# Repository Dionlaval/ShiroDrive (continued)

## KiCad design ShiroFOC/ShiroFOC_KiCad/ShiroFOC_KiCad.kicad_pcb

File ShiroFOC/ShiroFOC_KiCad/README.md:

# ShiroFOC A1-Drawing - schematic ready for prototype PCB layout

**P1 revision notes:** see [../PCB_REVISION_LIST_P1.md](../docs/PCB_REVISION_LIST_P1.md). H1-H4 are now in the schematic; the P0 PCB still awaits the mounting holes and placement revision. Earlier parity reports and release PDFs/ZIPs predate this change.

**PCB P0 placement is now available:** all 260 footprints on an 80 × 80 mm rounded-square, four-layer board. See [placement notes and previews](../docs/PCB_PLACEMENT_P0.md). Open the existing `.kicad_pcb`; it remains unrouted. The prior schematic release archives and manifests describe the earlier release, not this placement checkpoint.

Open `ShiroFOC_KiCad.kicad_pro` in **KiCad 9**. The project contains 12 native schematic sheets with connected functional blocks and project-local symbols/critical footprints. Standard footprints resolve through KiCad 9's installed libraries. A1-Drawing preserves all A0 electrical connections, components, values, MPNs, footprints and DNP choices.

Start with [design review](../docs/DESIGN_REVIEW_REV_A.md), [PCB layout handoff](../docs/PCB_LAYOUT_HANDOFF.md), and [firmware contract](../docs/FIRMWARE_BRINGUP_CONTRACT.md). No PCB has been routed. Current/voltage goals still require hardware qualification; the review identifies ripple, thermal, USB-power and braking limits.

## Release contents

- `libs/ShiroFOC_Redraw.kicad_sym`: functional symbols, including multi-unit STSPIN and analog switches, with complete physical pin mapping.
- `libs/ShiroFOC.pretty`: four datasheet-derived footprint types.
- `outputs/ShiroFOC_Rev_A_Schematic.pdf`: reviewed, searchable 12-page schematic (ten A3 and two A4 pages).
- `outputs/ShiroFOC_Rev_A_BOM.csv`: one row per reference, including DNP and procurement specifications.
- `outputs/ShiroFOC_Rev_A.net`: KiCad XML netlist.
- `outputs/erc_rev_a.json`, `validation_report.json`, `footprint_audit.json`, `footprint_pad_audit.csv`: release verification evidence.
- `outputs/electrical_calculations.json`: current-sense, brake-threshold, bus and rail calculations.
- `outputs/visual_review.json`, `release_manifest.json`: reviewed PDF/pages and SHA-256 release hashes.
- `outputs/net_name_aliases.json`: maps KiCad's local/hierarchical net names to the A0 names used by the handoff. Complete physical pin groups are verified independently of naming.
- `../review_baselines/A0_before_redraw/`: frozen connectivity and BOM used by the validator.

## Rebuild

Requires Python 3.12+ and KiCad 9 CLI, plus a Python interpreter containing `pcbnew`. From the ShiroFOC directory:

```sh
python3 tools/release_rev_a.py
```

On macOS the script discovers the standard `/Applications/KiCad/` installation. Other installations can set `KICAD_CLI`, `KICAD_PYTHON`, and `KICAD9_FOOTPRINT_DIR`. `KICAD_PYTHON` must import pcbnew. Set `FONTCONFIG_FILE` to a valid local fontconfig configuration if that installation needs one for headless PDF export.

`generate_rev_a.py` retains the electrical definitions. `native_rev_a.py` now delegates to `redraw_rev_a.py`; `redraw_core.py`, `redraw_power.py`, `redraw_analog.py` and `redraw_interfaces.py` define the connected drawings using `redraw_engine.py`. No legacy GUI conversion is needed. UUIDs are stable between redraw builds. **Rebuild overwrites generated native sheets and the redraw symbol library.** If editing in KiCad, also reconcile those changes into the layout modules before rebuilding. The checked-in custom footprints, project settings and handoff documents are preserved.

The overview contains navigable child sheets and graphic system connections. Circuit boundaries use named global ports; local circuits use wires and junctions. STSPIN units A/B/C/D/E/F remain one physical U301. See [redraw review](../docs/SCHEMATIC_REDRAW_REVIEW.md) for the sheet map and validation scope.

Rebuild regenerates machine checks but does not perform visual approval. Render and inspect the new PDF; refresh `visual_review.json` with its exact hash only after review, then run `python3 tools/release_rev_a.py --manifest-only`. That final command checks the visual hash and writes the release manifest. Keep review status separate from a successful CLI export.

## Start PCB layout

Continue from the existing P0 PCB. Use Update PCB from Schematic when synchronizing subsequent schematic changes. Keep all DNP footprints on-board; fitted state is controlled by the native DNP property and Assembly field. Follow the handoff for Kelvin routing, DC-link return points, live VIN thermal pads, optional termination and external connector restrictions. Preserve U901's documented thermal-drill adjustment when updating footprints. Resolve mechanical fit, copper/current sizing, DRC and fabrication details during PCB work.

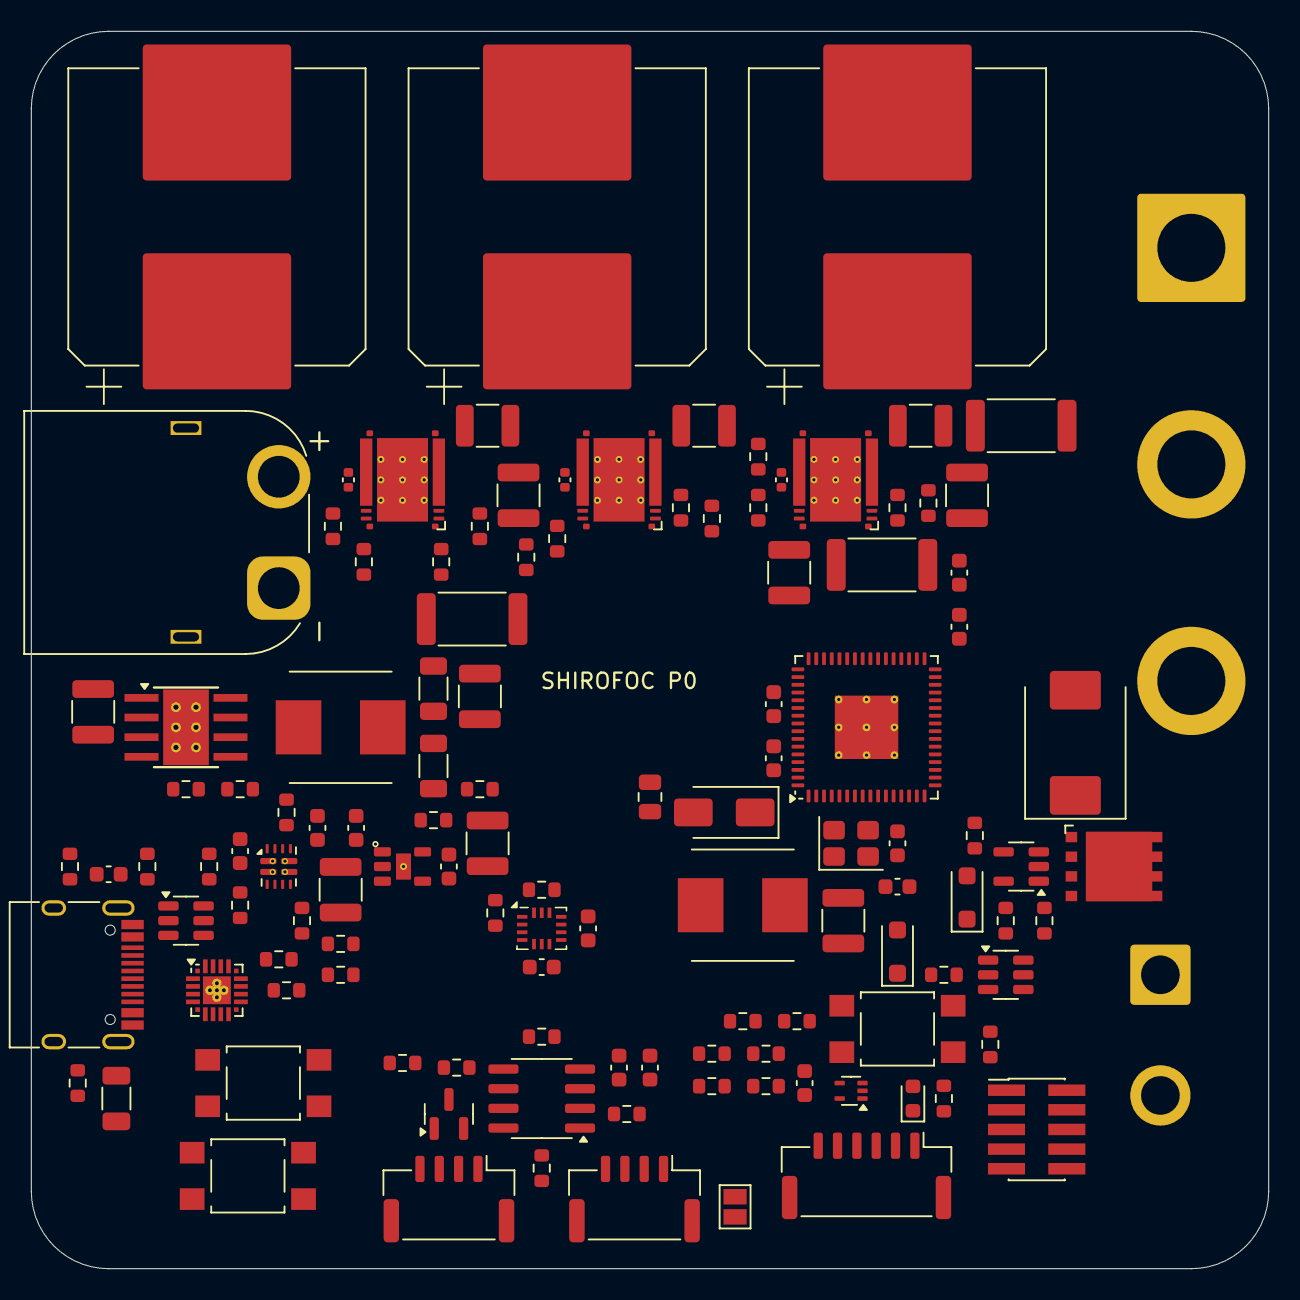
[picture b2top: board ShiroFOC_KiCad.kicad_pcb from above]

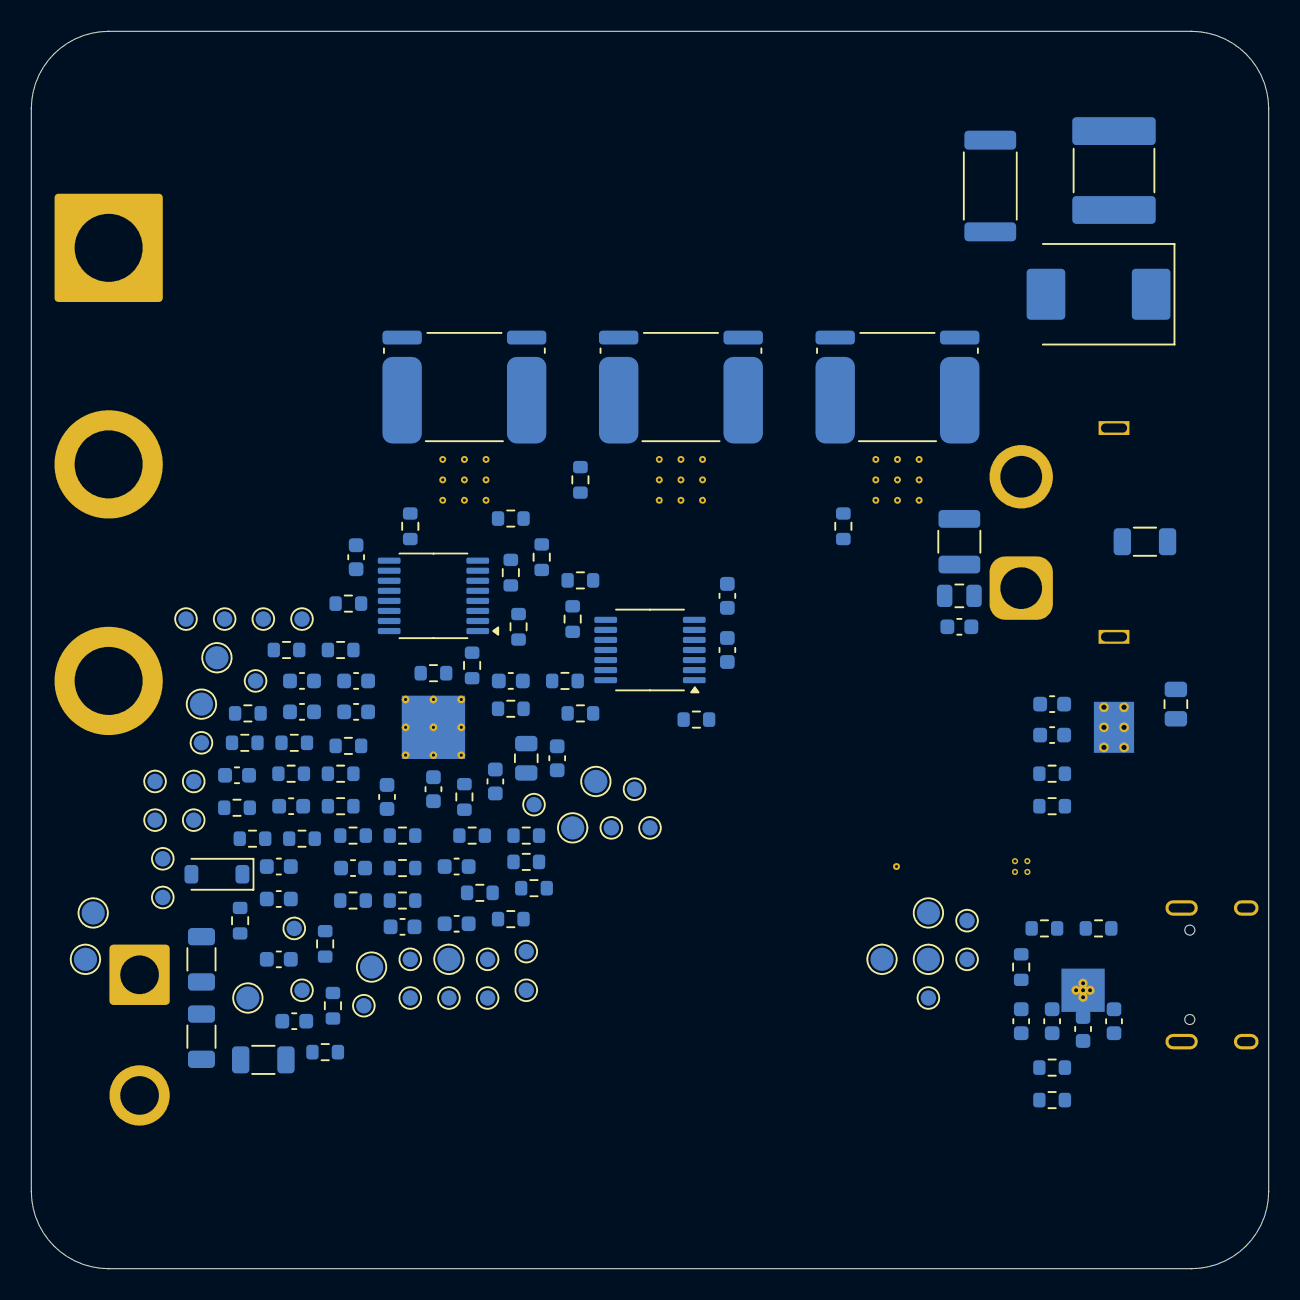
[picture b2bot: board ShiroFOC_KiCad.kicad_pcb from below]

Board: 4 copper layers, 80.0 x 80.0 mm, 260 parts (138 on the bottom side), 148 nets, no tracks yet.

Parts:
C101, C102, C103: 680uF 63V; CP_Elec_18x17.5
C104: 4.7uF 100V X7R; C_1210_3225Metric
C105: 100nF 100V X7R; C_0805_2012Metric
C106: 10nF 100V C0G; C_0603_1608Metric
C107: RC DAMP C - TUNE; C_2220_5750Metric
C108, C314, C711, C712, C713: 10nF; C_0603_1608Metric
C201: 2.2uF 100V X7R; C_1210_3225Metric
C202: 220nF 100V X7R; C_0805_2012Metric
C203, C209, C211, C301, C303, C305, C307, C310, C503, C601, C603, C701, C702, C801, C902, C904: 100nF; C_0603_1608Metric
C204, C304, C306, C602, C802: 1uF; C_0603_1608Metric
C205, C206, C210: 22uF 10V X7R; C_1210_3225Metric
C207: 4.7nF 2kV; C_1206_3216Metric
C208: 1uF 10V; C_0603_1608Metric
C212, C213: 2.2uF 10V X7R; C_0603_1608Metric
C302: 10uF 10V; C_0805_2012Metric
C308, C309: 10pF C0G; C_0603_1608Metric
C311: 220nF 100V; C_0805_2012Metric
C312: 10uF 25V X7R; C_1210_3225Metric
C313, C411, C421, C431, C502: 100nF 25V; C_0603_1608Metric
C412, C422, C432: 1uF 100V X7R; C_1210_3225Metric
C413, C423, C433: SNUBBER C TUNE; C_1210_3225Metric
C414, C424, C434: 47pF C0G; C_0603_1608Metric
C415, C425, C435: 10nF 100V X7S; C_0402_1005Metric
C501: 1uF 25V; C_0603_1608Metric
C504: 1nF C0G; C_0603_1608Metric
C604: 100nF 50V; C_0603_1608Metric
C901, C903: 4.7uF 10V; C_0603_1608Metric
D101: VM TVS - SELECT AFTER TEST; D_SMC
D301: RED; LED_0603_1608Metric
D302: STPS1H100A; D_SMA
D501: BZT52C12 12V; D_SOD-123
D502, D503: BAT54H; D_SOD-123F
D504: B5100C 100V 5A; D_SMC
D601: TPD3E001DRLR 3-line ESD; Texas_R-PDSO-N5_DRL-5
D801: PESD2CANFD24V-T; SOT-23
J101: AMASS XT60PW-M; AMASS_XT60PW-M_1x02_P7.20mm_Horizontal
J201: USB-C service; USB_C_Receptacle_HRO_TYPE-C-31-M-12
J401: MOTOR U/V/W; SolderWire-6sqmm_1x03_P14mm_D3.5mm_OD7mm
J501: BRAKE RESISTOR; SolderWire-2sqmm_1x02_P7.8mm_D2mm_OD3.9mm
J601: EXT ENCODER / HALL; JST_GH_BM06B-GHS-TBT_1x06-1MP_P1.25mm_Vertical
J801: CAN 1; JST_GH_BM04B-GHS-TBT_1x04-1MP_P1.25mm_Vertical
J802: CAN 2; JST_GH_BM04B-GHS-TBT_1x04-1MP_P1.25mm_Vertical
J1001: ARM Cortex SWD 10-pin; PinHeader_2x05_P1.27mm_Vertical_SMD
JP801: TERM ENABLE; SolderJumper-2_P1.3mm_Open_Pad1.0x1.5mm
L201, L301: 22uH / 2.75A; WE_LHMI_7050_74437349220
Q401, Q402, Q403: CSD88599Q5DC; CSD88599Q5DC_DMM0022A
Q501: CSD19531Q5A 100V; CSD19531Q5A_Q5A_DQJ0008A
R101: 470k 0.25W; R_1206_3216Metric
R102: RC DAMP R - TUNE; R_2512_6332Metric
R103, R104: 270k 0.1% 100V; R_1206_3216Metric
R105: 27k 0.1%; R_0603_1608Metric
R106, R304, R312, R711, R712, R713, R901, R1001: 1k; R_0603_1608Metric
R201: 100k 1%; R_0603_1608Metric
R202: 24.9k 1%; R_0603_1608Metric
R203, R204: 5.1k; R_0603_1608Metric
R205, R301, R302, R412, R422, R432: 0R; R_0603_1608Metric
R206: 15.0k 1%; R_0603_1608Metric
R207, R209, R211, R213: 5.10k 1%; R_0603_1608Metric
R208: 10.0k 1%; R_0603_1608Metric
R210, R212: 21.0k 1%; R_0603_1608Metric
R214: 80.6k 1%; R_0603_1608Metric
R215, R305, R306, R307, R308, R309, R311, R501, R504, R505, R801, R805: 10k; R_0603_1608Metric
R303, R310, R413, R414, R423, R424, R433, R434: 100k; R_0603_1608Metric
R313, R314: 22R; R_0603_1608Metric
R410, R420, R430, R441, R442, R443: 56k 0.1%; R_0603_1608Metric
R411, R421, R431, R503: 4.7R; R_0603_1608Metric
R415, R425, R435: SNUBBER R TUNE; R_2512_6332Metric
R416, R426, R436: BVR-Z-R0005 0.5mR; R_Shunt_Isabellenhuette_BVR4026
R417, R418, R427, R428, R437, R438: 1k 0.1%; R_0603_1608Metric
R419, R429, R439: 28k 0.1%; R_0603_1608Metric
R502, R601, R602, R603, R611, R714: 33R; R_0603_1608Metric
R506, R507, R508: 150k 0.1% 100V; R_1206_3216Metric
R509: 12.7k 0.1%; R_0603_1608Metric
R510: 1M 0.1%; R_0603_1608Metric
R604: 0R; external load <=25mA; R_0603_1608Metric
R605, R606, R607, R902, R903: 100R; R_0603_1608Metric
R608, R609, R610: 10k DNP Hall pull-up; R_0603_1608Metric
R701, R702, R703: 4.7k 1%; R_0603_1608Metric
R802: 120R 1%; R_0603_1608Metric
R803: 0R CANH link; R_0603_1608Metric
R804: 0R CANL link; R_0603_1608Metric
R904: 22.1k 1%; R_0603_1608Metric
R905: 47.5k 1%; R_0603_1608Metric
SW301, SW1002: RESET; SW_SPST_TL3305A
SW1001: BOOT0; SW_SPST_TL3305A
TH701, TH702, TH703: 10k NTC B3380; R_0603_1608Metric
TP101: VM; TestPoint_Pad_D1.5mm
TP102: GND; TestPoint_Pad_D1.5mm
TP103: VBUS_SENSE; TestPoint_Pad_D1.5mm
TP201: 5V_BAT; TestPoint_Pad_D1.5mm
TP202: 5V_USB; TestPoint_Pad_D1.5mm
TP203: 5V_SYS; TestPoint_Pad_D1.5mm
TP204: 3V3; TestPoint_Pad_D1.5mm
TP301: VCC; TestPoint_Pad_D1.5mm
TP302: SCREF; TestPoint_Pad_D1.5mm
TP303: NRST; TestPoint_Pad_D1.5mm
TP501: BRAKE_GATE; TestPoint_Pad_D1.5mm
TP502: BRK_SW; TestPoint_Pad_D1.5mm
TP701: NTC_A; TestPoint_Pad_D1.0mm
TP702: NTC_B; TestPoint_Pad_D1.0mm
TP703: NTC_C; TestPoint_Pad_D1.0mm
TP901: USB_UART_TX; TestPoint_Pad_D1.0mm
TP902: USB_UART_RX; TestPoint_Pad_D1.0mm
TP903: GND; TestPoint_Pad_D1.0mm
TP1001: VM; TestPoint_Pad_D1.0mm
TP1002: VCC; TestPoint_Pad_D1.0mm
TP1003: 5V_BAT; TestPoint_Pad_D1.0mm
TP1004: 5V_USB; TestPoint_Pad_D1.0mm
TP1005: 5V_SYS; TestPoint_Pad_D1.0mm
TP1006: 3V3; TestPoint_Pad_D1.0mm
TP1007: NRST; TestPoint_Pad_D1.0mm
TP1008: SWDIO; TestPoint_Pad_D1.0mm
TP1009: SWCLK; TestPoint_Pad_D1.0mm
TP1010: SPI3_SCK; TestPoint_Pad_D1.0mm
TP1011: SPI3_MISO; TestPoint_Pad_D1.0mm
TP1012: SPI3_MOSI; TestPoint_Pad_D1.0mm
TP1013: FDCAN1_TX; TestPoint_Pad_D1.0mm
TP1014: FDCAN1_RX; TestPoint_Pad_D1.0mm
TP1015: FEEDBACK_A_H1; TestPoint_Pad_D1.0mm
TP1016: FEEDBACK_B_H2; TestPoint_Pad_D1.0mm
TP1018: OPO_U1; TestPoint_Pad_D1.0mm
TP1019: OPO_V1; TestPoint_Pad_D1.0mm
TP1020: OPO_W1; TestPoint_Pad_D1.0mm
TP1021: SPARE_GPIO_1; TestPoint_Pad_D1.0mm
TP1022: CAN_STB; TestPoint_Pad_D1.0mm
TP1023: SPARE_GPIO_3; TestPoint_Pad_D1.0mm
TP1024: SPARE_TIM_GPIO; TestPoint_Pad_D1.0mm
U201: LMR36510FADDAR; Texas_HTSOP-8-1EP_3.9x4.9mm_P1.27mm_EP2.95x4.9mm_Mask2.4x3.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
U202: USBLC6-2SC6; SOT-23-6
U203: TPS2121RUXR; Texas_VQFN-HR-12_2x2.5mm_P0.5mm_ThermalVias
U204: TLV75533PDYDR; Texas_DYD0005A_SOT23-5
U301: STSPIN32G4; QFN-64-1EP_9x9mm_P0.5mm_EP4.1x4.1mm_ThermalVias
U501: UCC27517ADBVR; SOT-23-5
U502: TLV3012BIDBVR; SOT-23-6
U601: AS5047P-ATSM; TSSOP-14_4.4x5mm_P0.65mm
U602: TMUX1574PW; TSSOP-16_4.4x5mm_P0.65mm
U701: BMI323; Bosch_LGA-14_3x2.5mm_P0.5mm
U801: TCAN3413DR; SOIC-8_3.9x4.9mm_P1.27mm
U901: CP2102N-A02-GQFN20; SiliconLabs_QFN-20-1EP_3x3mm_P0.5mm_EP1.8x1.8mm_ThermalVias
Y301: 24MHz 7pF; Crystal_SMD_3225-4Pin_3.2x2.5mm

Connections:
3V3: C213.1, C301.1, C302.1, C307.1, C503.1, C601.1, C602.1, C603.1, C701.1, C702.1, C801.1, C802.1, C901.1, C902.1, C903.1, C904.1, J1001.1, R215.1, R301.1, R303.1, R304.1, R305.1, R308.1, R309.1, R310.1, R604.1, R608.1, R609.1, R610.1, R701.1, R702.1, R703.1, R801.1, R805.1, R901.1, SW1001.2, TP204.1, TP1006.1, U204.5, U301.1, U301.2, U301.64, U502.6, U601.11, U601.12, U602.16, U701.5, U701.8, U801.3, U801.5, U901.6, U901.7
5V_BAT: C205.1, C206.1, L201.2, R201.1, R206.1, R210.1, TP201.1, TP1003.1, U203.7
5V_SYS: C210.1, C211.1, C212.1, TP203.1, TP1005.1, U203.1, U203.8, U204.1, U204.3
5V_USB: C208.1, R205.2, R208.1, R212.1, TP202.1, TP1004.1, U203.2
5V_USB_RAW: J201.A4, J201.A9, J201.B4, J201.B9, R205.1, R904.1, U202.5
/5 V / 3.3 V power/5V_FB: R201.2, R202.1, U201.5
/Brake chopper/BRAKE_OV_CMD: D503.2, R510.1, U502.1
/Brake chopper/BRAKE_PWM_DRV: D502.1, D503.1, R505.1, U501.3
/CAN interface/CANH_BUS: D801.1, J801.3, J802.3, R802.1, R803.2
/CAN interface/CANH_INT: R803.1, U801.7
/CAN interface/CANL_BUS: D801.2, J801.2, J802.2, JP801.2, R804.2
/CAN interface/CANL_INT: R804.1, U801.6
/CAN interface/CAN_SHIELD: J801.4, J802.4
/CAN interface/CAN_TERM_MID: JP801.1, R802.2
/Current / temperature/NTC_A_RAW: R701.2, R711.1, TH701.1
/Current / temperature/NTC_B_RAW: R702.2, R712.1, TH702.1
/Current / temperature/NTC_C_RAW: R703.2, R713.1, TH703.1
/Current / temperature/OPN_U1: C414.2, R418.2, R419.2, U301.16
/Current / temperature/OPN_V1: C424.2, R428.2, R429.2, U301.22
/Current / temperature/OPN_W1: C434.2, R438.2, R439.2, U301.25
/Current / temperature/OPP_U1: R410.2, R417.2, R441.1, U301.14
/Current / temperature/OPP_V1: R420.2, R427.2, R442.1, U301.20
/Current / temperature/OPP_W1: R430.2, R437.2, R443.1, U301.23
/Feedback selection/3V3_EXT_FB: J601.1, R604.2
/Feedback selection/FB_ESD_RAIL: C604.1, D601.5
/Feedback selection/MUX_EXT_A: R605.2, R608.2, U602.3
/Feedback selection/MUX_EXT_B: R606.2, R609.2, U602.6
/Feedback selection/MUX_EXT_I: R607.2, R610.2, U602.10
/MCU / clock / SWD/NRST: C310.1, J1001.10, R303.2, SW301.1, SW1002.1, TP303.1, TP1007.1, U301.8
/MCU / clock / SWD/SPARE_GPIO_1: TP1021.1, U301.5
/MCU / clock / SWD/SPARE_GPIO_3: TP1023.1, U301.3
/MCU / clock / SWD/SPARE_TIM_GPIO: TP1024.1, U301.44
/SPI sensors/AS5047_MISO_RAW: R611.1, U601.3
/SPI sensors/BMI323_MISO_RAW: R714.1, U701.1
/SPI sensors/ENC_ON_A: R601.1, U601.7
/SPI sensors/ENC_ON_B: R602.1, U601.6
/SPI sensors/ENC_ON_I: R603.1, U601.14
/SPI sensors/SPI3_MOSI: R314.2, TP1012.1, U601.4, U701.14
/SPI sensors/SPI3_SCK: R313.2, TP1010.1, U601.2, U701.13
/Three-phase bridge/SHUNT_U_FORCE_P: C415.2, Q401.12, Q401.13, Q401.14, Q401.15, Q401.16, Q401.17, Q401.18, Q401.19, Q401.20, R414.2, R416.1
/Three-phase bridge/SHUNT_V_FORCE_P: C425.2, Q402.12, Q402.13, Q402.14, Q402.15, Q402.16, Q402.17, Q402.18, Q402.19, Q402.20, R424.2, R426.1
/Three-phase bridge/SHUNT_W_FORCE_P: C435.2, Q403.12, Q403.13, Q403.14, Q403.15, Q403.16, Q403.17, Q403.18, Q403.19, Q403.20, R434.2, R436.1
/USB service/CP2102_RST_N: R901.2, U901.9
/USB service/CP2102_VBUS_SENSE: R904.2, R905.1, U901.8
/USB service/UART_BRIDGE_RX: R903.2, U901.17
/USB service/UART_BRIDGE_TX: R902.1, U901.18
/USB service/USB_CC1: J201.A5, R203.1
/USB service/USB_CC2: J201.B5, R204.1
/USB service/USB_DM: U202.6, U901.5
/USB service/USB_DM_CONN: J201.A7, J201.B7, U202.1
/USB service/USB_DP: U202.4, U901.4
/USB service/USB_DP_CONN: J201.A6, J201.B6, U202.3
/USB service/USB_SHIELD: C207.1, J201.S1
AS5047P_CS_N: R309.2, U301.51, U601.1
BOOT1: C411.1, U301.41
BOOT2: C421.1, U301.38
BOOT3: C431.1, U301.35
BRAKE_PWM: R501.1, R502.1, U301.60
CAN_STB: R801.2, TP1022.1, U301.28, U801.8
FDCAN1_RX: TP1014.1, U301.47, U801.4
FDCAN1_TX: R805.2, TP1013.1, U301.48, U801.1
FEEDBACK_A_H1: TP1015.1, U301.57, U602.4
FEEDBACK_B_H2: TP1016.1, U301.58, U602.7
FEEDBACK_ENABLE_N: R305.2, U301.4, U602.15
FEEDBACK_I_H3: R307.1, R1001.1, U301.59, U602.9
FEEDBACK_SELECT: R306.1, U301.53, U602.1
GHS1: R411.1, U301.43
GHS2: R421.1, U301.40
GHS3: R431.1, U301.37
GLS1: R412.1, U301.29
GLS2: R422.1, U301.30
GLS3: R432.1, U301.31
GND: C101.2, C102.2, C103.2, C104.2, C105.2, C106.2, C107.2, C108.2, C201.2, C202.2, C204.2, C205.2, C206.2, C207.2, C208.2, C209.2, C210.2, C211.2, C212.2, C213.2, C301.2, C302.2, C303.2, C304.2, C305.2, C306.2, C307.2, C308.2, C309.2, C310.2, C311.2, C312.2, C313.2, C314.2, C412.2, C413.2, C422.2, C423.2, C432.2, C433.2, C501.2, C502.2, C503.2, C504.2, C601.2, C602.2, C603.2, C604.2, C701.2, C702.2, C711.2, C712.2, C713.2, C801.2, C802.2, C901.2, C902.2, C903.2, C904.2, D101.2, D302.2, D501.2, D601.3, D801.3, J101.1, J201.A1, J201.A12, J201.B1, J201.B12, J601.2, J801.1, J802.1, J1001.3, J1001.5, J1001.9, Q501.1, Q501.2, Q501.3, R101.2, R105.2, R202.2, R203.2, R204.2, R207.2, R209.2, R211.2, R213.2, R214.2, R306.2, R307.2, R311.2, R416.4, R426.4, R436.4, R441.2, R442.2, R443.2, R501.2, R504.2, R505.2, R509.2, R905.2, SW301.2, SW1002.2, TH701.2, TH702.2, TH703.2, TP102.1, TP903.1, U201.1, U201.9, U202.2, U203.12, U204.2, U301.32, U301.65, U501.2, U501.4, U502.2, U601.5, U601.13, U602.8, U701.6, U701.7, U801.2, U901.3, U901.12, U901.21, Y301.2, Y301.4
IMU_CS_N: R308.2, U301.21, U701.12
IMU_INT1: U301.17, U701.4
IMU_INT2: U301.18, U701.9
MUX_ON_A: R601.2, U602.2
MUX_ON_B: R602.2, U602.5
MUX_ON_I: R603.2, U602.11
NTC_PHASE_A: C711.1, R711.2, TP701.1, U301.12
NTC_PHASE_B: C712.1, R712.2, TP702.1, U301.9
NTC_PHASE_C: C713.1, R713.2, TP703.1, U301.10
unnamed: C107.1, R102.2
unnamed: C413.1, R415.2
unnamed: C423.1, R425.2
unnamed: C433.1, R435.2
unnamed: D301.2, R304.2
unnamed: D301.1, U301.11
unnamed: D302.1, L301.1, U301.62
unnamed: D501.1, Q501.4, R503.2, R504.1, TP501.1
unnamed: D502.2, R502.2
unnamed: D504.2, J501.2, Q501.5, Q501.6, Q501.7, Q501.8, TP502.1
unnamed: D601.1, J601.3, R605.1
unnamed: D601.2, J601.4, R606.1
unnamed: D601.4, J601.5, R607.1
unnamed: Q401.1, R411.2, R413.1
unnamed: Q401.22, R412.2, R414.1
unnamed: Q402.1, R421.2, R423.1
unnamed: Q402.22, R422.2, R424.1
unnamed: Q403.1, R431.2, R433.1
unnamed: Q403.22, R432.2, R434.1
unnamed: R103.2, R104.1
unnamed: R104.2, R105.1, R106.1
unnamed: R310.2, R311.1, R312.1
unnamed: R506.2, R507.1
unnamed: R507.2, R508.1
unnamed: R1001.2, SW1001.1
unnamed: C203.1, U201.7
unnamed: C203.2, L201.1, U201.8
unnamed: C204.1, U201.6
unnamed: R208.2, R209.1, U203.3
unnamed: R214.1, U203.10
unnamed: R210.2, R211.1, U203.5
unnamed: R212.2, R213.1, U203.4
unnamed: R206.2, R207.1, U203.6
unnamed: C209.1, U203.11
unnamed: J1001.2, TP1008.1, U301.49
unnamed: J1001.4, TP1009.1, U301.50
unnamed: C308.1, U301.6, Y301.1
unnamed: C309.1, U301.7, Y301.3
unnamed: C314.1, R312.2, TP302.1, U301.52
unnamed: R503.1, U501.5
unnamed: C504.1, R508.2, R509.1, R510.2, U502.3
unnamed: U502.4, U502.5
OPO_U1: C414.1, R419.1, TP1018.1, U301.15
OPO_V1: C424.1, R429.1, TP1019.1, U301.19
OPO_W1: C434.1, R439.1, TP1020.1, U301.24
OUT1: C411.2, J401.1, Q401.2, Q401.3, Q401.4, Q401.5, Q401.6, Q401.7, Q401.8, Q401.9, Q401.10, Q401.11, R413.2, R415.1, U301.42
OUT2: C421.2, J401.2, Q402.2, Q402.3, Q402.4, Q402.5, Q402.6, Q402.7, Q402.8, Q402.9, Q402.10, Q402.11, R423.2, R425.1, U301.39
OUT3: C431.2, J401.3, Q403.2, Q403.3, Q403.4, Q403.5, Q403.6, Q403.7, Q403.8, Q403.9, Q403.10, Q403.11, R433.2, R435.1, U301.36
PWR_SOURCE_STATUS: R215.2, U203.9
SHUNT_U_SENSE_N: R416.3, R418.1
SHUNT_U_SENSE_P: R416.2, R417.1
SHUNT_V_SENSE_N: R426.3, R428.1
SHUNT_V_SENSE_P: R426.2, R427.1
SHUNT_W_SENSE_N: R436.3, R438.1
SHUNT_W_SENSE_P: R436.2, R437.1
SPI3_MISO: R611.2, R714.2, TP1011.1, U301.55
SPI3_MOSI_MCU: R314.1, U301.56
SPI3_SCK_MCU: R313.1, U301.54
USB_UART_RX: R902.2, TP902.1, U301.46
USB_UART_TX: R903.1, TP901.1, U301.45
VBUS_MUX_IN: R106.2, U602.13, U602.14
VBUS_SENSE: C108.1, TP103.1, U301.13, U602.12
VCC: C312.1, C313.1, C501.1, C502.1, L301.2, TP301.1, TP1002.1, U301.63, U501.1
VDDA: C303.1, C304.1, R301.2, R302.1, U301.27
VM: C101.1, C102.1, C103.1, C104.1, C105.1, C106.1, C201.1, C202.1, C311.1, C412.1, C415.1, C422.1, C425.1, C432.1, C435.1, D101.1, D504.1, J101.2, J501.1, Q401.27, Q402.27, Q403.27, R101.1, R102.1, R103.1, R506.1, TP101.1, TP1001.1, U201.2, U201.3, U301.61
VREF+: C305.1, C306.1, R302.2, R410.1, R420.1, R430.1, U301.26

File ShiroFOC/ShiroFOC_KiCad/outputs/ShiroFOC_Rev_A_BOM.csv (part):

"Reference","Value","Footprint","MPN","Assembly","Rating","Procurement","Datasheet","DNP"
"C101","680uF 63V","Capacitor_SMD:CP_Elec_18x17.5","EEVFK1J681M","FIT","See Value; generic low-voltage passives: R >=0.1 W / 50 V, C >=16 V X7R unless specified","","",""
"C102","680uF 63V","Capacitor_SMD:CP_Elec_18x17.5","EEVFK1J681M","FIT","See Value; generic low-voltage passives: R >=0.1 W / 50 V, C >=16 V X7R unless specified","","",""
"C103","680uF 63V","Capacitor_SMD:CP_Elec_18x17.5","EEVFK1J681M","FIT","See Value; generic low-voltage passives: R >=0.1 W / 50 V, C >=16 V X7R unless specified","","",""
"C104","4.7uF 100V X7R","Capacitor_SMD:C_1210_3225Metric","","FIT","See Value; generic low-voltage passives: R >=0.1 W / 50 V, C >=16 V X7R unless specified","Select to specification: 4.7uF 100V X7R; C_1210_3225Metric","",""
"C105","100nF 100V X7R","Capacitor_SMD:C_0805_2012Metric","","FIT","See Value; generic low-voltage passives: R >=0.1 W / 50 V, C >=16 V X7R unless specified","Select to specification: 100nF 100V X7R; C_0805_2012Metric","",""
"C106","10nF 100V C0G","Capacitor_SMD:C_0603_1608Metric","","FIT","See Value; generic low-voltage passives: R >=0.1 W / 50 V, C >=16 V X7R unless specified","Select to specification: 10nF 100V C0G; C_0603_1608Metric","",""
"C107","RC DAMP C - TUNE","Capacitor_SMD:C_2220_5750Metric","","DNP","See Value; generic low-voltage passives: R >=0.1 W / 50 V, C >=16 V X7R unless specified","Select to specification: RC DAMP C - TUNE; C_2220_5750Metric","","DNP"
"C108","10nF","Capacitor_SMD:C_0603_1608Metric","","FIT","See Value; generic low-voltage passives: R >=0.1 W / 50 V, C >=16 V X7R unless specified","Select to specification: 10nF; C_0603_1608Metric","",""
"C201","2.2uF 100V X7R","Capacitor_SMD:C_1210_3225Metric","","FIT","See Value; generic low-voltage passives: R >=0.1 W / 50 V, C >=16 V X7R unless specified","Select to specification: 2.2uF 100V X7R; C_1210_3225Metric","",""
"C202","220nF 100V X7R","Capacitor_SMD:C_0805_2012Metric","","FIT","See Value; generic low-voltage passives: R >=0.1 W / 50 V, C >=16 V X7R unless specified","Select to specification: 220nF 100V X7R; C_0805_2012Metric","",""
"C203","100nF","Capacitor_SMD:C_0603_1608Metric","","FIT","See Value; generic low-voltage passives: R >=0.1 W / 50 V, C >=16 V X7R unless specified","Select to specification: 100nF; C_0603_1608Metric","",""
"C204","1uF","Capacitor_SMD:C_0603_1608Metric","","FIT","See Value; generic low-voltage passives: R >=0.1 W / 50 V, C >=16 V X7R unless specified","Select to specification: 1uF; C_0603_1608Metric","",""
"C205","22uF 10V X7R","Capacitor_SMD:C_1210_3225Metric","","FIT","See Value; generic low-voltage passives: R >=0.1 W / 50 V, C >=16 V X7R unless specified","Select to specification: 22uF 10V X7R; C_1210_3225Metric","",""
"C206","22uF 10V X7R","Capacitor_SMD:C_1210_3225Metric","","FIT","See Value; generic low-voltage passives: R >=0.1 W / 50 V, C >=16 V X7R unless specified","Select to specification: 22uF 10V X7R; C_1210_3225Metric","",""
"C207","4.7nF 2kV","Capacitor_SMD:C_1206_3216Metric","","DNP","See Value; generic low-voltage passives: R >=0.1 W / 50 V, C >=16 V X7R unless specified","Select to specification: 4.7nF 2kV; C_1206_3216Metric","","DNP"
"C208","1uF 10V","Capacitor_SMD:C_0603_1608Metric","","FIT","See Value; generic low-voltage passives: R >=0.1 W / 50 V, C >=16 V X7R unless specified","Select to specification: 1uF 10V; C_0603_1608Metric","",""
"C209","100nF","Capacitor_SMD:C_0603_1608Metric","","FIT","See Value; generic low-voltage passives: R >=0.1 W / 50 V, C >=16 V X7R unless specified","Select to specification: 100nF; C_0603_1608Metric","",""
"C210","22uF 10V X7R","Capacitor_SMD:C_1210_3225Metric","","FIT","See Value; generic low-voltage passives: R >=0.1 W / 50 V, C >=16 V X7R unless specified","Select to specification: 22uF 10V X7R; C_1210_3225Metric","",""
"C211","100nF","Capacitor_SMD:C_0603_1608Metric","","FIT","See Value; generic low-voltage passives: R >=0.1 W / 50 V, C >=16 V X7R unless specified","Select to specification: 100nF; C_0603_1608Metric","",""
"C212","2.2uF 10V X7R","Capacitor_SMD:C_0603_1608Metric","","FIT","See Value; generic low-voltage passives: R >=0.1 W / 50 V, C >=16 V X7R unless specified","Select to specification: 2.2uF 10V X7R; C_0603_1608Metric","",""
"C213","2.2uF 10V X7R","Capacitor_SMD:C_0603_1608Metric","","FIT","See Value; generic low-voltage passives: R >=0.1 W / 50 V, C >=16 V X7R unless specified","Select to specification: 2.2uF 10V X7R; C_0603_1608Metric","",""
"C301","100nF","Capacitor_SMD:C_0603_1608Metric","","FIT","See Value; generic low-voltage passives: R >=0.1 W / 50 V, C >=16 V X7R unless specified","Select to specification: 100nF; C_0603_1608Metric","",""
"C302","10uF 10V","Capacitor_SMD:C_0805_2012Metric","","FIT","See Value; generic low-voltage passives: R >=0.1 W / 50 V, C >=16 V X7R unless specified","Select to specification: 10uF 10V; C_0805_2012Metric","",""
"C303","100nF","Capacitor_SMD:C_0603_1608Metric","","FIT","See Value; generic low-voltage passives: R >=0.1 W / 50 V, C >=16 V X7R unless specified","Select to specification: 100nF; C_0603_1608Metric","",""
"C304","1uF","Capacitor_SMD:C_0603_1608Metric","","FIT","See Value; generic low-voltage passives: R >=0.1 W / 50 V, C >=16 V X7R unless specified","Select to specification: 1uF; C_0603_1608Metric","",""
"C305","100nF","Capacitor_SMD:C_0603_1608Metric","","FIT","See Value; generic low-voltage passives: R >=0.1 W / 50 V, C >=16 V X7R unless specified","Select to specification: 100nF; C_0603_1608Metric","",""
"C306","1uF","Capacitor_SMD:C_0603_1608Metric","","FIT","See Value; generic low-voltage passives: R >=0.1 W / 50 V, C >=16 V X7R unless specified","Select to specification: 1uF; C_0603_1608Metric","",""
"C307","100nF","Capacitor_SMD:C_0603_1608Metric","","FIT","See Value; generic low-voltage passives: R >=0.1 W / 50 V, C >=16 V X7R unless specified","Select to specification: 100nF; C_0603_1608Metric","",""
"C308","10pF C0G","Capacitor_SMD:C_0603_1608Metric","","FIT","See Value; generic low-voltage passives: R >=0.1 W / 50 V, C >=16 V X7R unless specified","Select to specification: 10pF C0G; C_0603_1608Metric","",""
"C309","10pF C0G","Capacitor_SMD:C_0603_1608Metric","","FIT","See Value; generic low-voltage passives: R >=0.1 W / 50 V, C >=16 V X7R unless specified","Select to specification: 10pF C0G; C_0603_1608Metric","",""
"C310","100nF","Capacitor_SMD:C_0603_1608Metric","","FIT","See Value; generic low-voltage passives: R >=0.1 W / 50 V, C >=16 V X7R unless specified","Select to specification: 100nF; C_0603_1608Metric","",""
"C311","220nF 100V","Capacitor_SMD:C_0805_2012Metric","","FIT","See Value; generic low-voltage passives: R >=0.1 W / 50 V, C >=16 V X7R unless specified","Select to specification: 220nF 100V; C_0805_2012Metric","",""
"C312","10uF 25V X7R","Capacitor_SMD:C_1210_3225Metric","","FIT","See Value; generic low-voltage passives: R >=0.1 W / 50 V, C >=16 V X7R unless specified","Select to specification: 10uF 25V X7R; C_1210_3225Metric","",""
"C313","100nF 25V","Capacitor_SMD:C_0603_1608Metric","","FIT","See Value; generic low-voltage passives: R >=0.1 W / 50 V, C >=16 V X7R unless specified","Select to specification: 100nF 25V; C_0603_1608Metric","",""
"C314","10nF","Capacitor_SMD:C_0603_1608Metric","","FIT","See Value; generic low-voltage passives: R >=0.1 W / 50 V, C >=16 V X7R unless specified","Select to specification: 10nF; C_0603_1608Metric","",""
"C411","100nF 25V","Capacitor_SMD:C_0603_1608Metric","","FIT","See Value; generic low-voltage passives: R >=0.1 W / 50 V, C >=16 V X7R unless specified","Select to specification: 100nF 25V; C_0603_1608Metric","",""
"C412","1uF 100V X7R","Capacitor_SMD:C_1210_3225Metric","","FIT","See Value; generic low-voltage passives: R >=0.1 W / 50 V, C >=16 V X7R unless specified","Select to specification: 1uF 100V X7R; C_1210_3225Metric","",""
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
